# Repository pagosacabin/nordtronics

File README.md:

# Nordtronics

Code, hardware designs, and CAD models from **Nordtronics** (Pagosa Springs, CO) —
an off-grid solar, battery, and IoT practice. Custom LiFePO4 battery builds,
off-grid solar installs, and wireless sensor systems (ESP32 / LoRa / MQTT /
Home Assistant).

## Layout

- `backend/` — wildfire pipeline: Mosquitto broker, ingest worker, read-only
  FastAPI service, and the deployment guide (`DEPLOY.md`).
- `firmware/wildfire-node-v1/` — unified LoRa wildfire node/base-station
  firmware (Heltec LoRa 32 V4).
- `android/companion-v0/` — Android companion app for the wildfire network.
- `website/` — nordtronics.io site.
- `docs/` — runbooks and design docs (`docs/wildfire/` for the wildfire net).
- `firmware/cistern-monitor/` — Tank-Monitor remote cistern level monitor:
  ESP32-S3 + SX1262 LoRa TX/RX pair, ultrasonic level sensing, MQTT/Home
  Assistant integration (`cistern_unified.ino`).
- `firmware/lora-display/` — LoRa radio experiments on Heltec LoRa V3 boards,
  including display and RF-preset sketches.
- `python/ultrasonic-sensors/` — MicroPython scripts for ultrasonic distance
  sensing with OLED/LCD output.
- `hardware/battery-pcb/` — KiCad project archives for the custom main battery
  PCB (JK BMS based LiFePO4 pack), including versioned iterations.
- `hardware/busbar/` — Busbar designs for EVE 280Ah cells.
- `cad/first-project/` — Early KiCad project archives.
- `cad/robotic-arm/` — Robotic arm 3D model (STEP).

Archived `.zip` files are kept as-is, preserving the original design history.
- `installs/solar/` — Off-grid solar + storage install notes.

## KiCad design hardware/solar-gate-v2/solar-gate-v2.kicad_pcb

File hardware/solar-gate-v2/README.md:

# Solar gate — temperature cutoff, Mark 1 Rev 2

An add-in module for the wildfire-node power path: `panel (+) → this board → Heltec V4
solar input`. It switches the panel feed off when the cell is too cold or too hot, using a
10 k B3950 NTC bonded to the cell, an LM393 window comparator and a TL431 reference. The
pass element is two back-to-back FQP27P06 pairs (common drain at `M`), so the board blocks
current in both directions when off — that is what makes `P` never beep to `SOLAR_OUT`.

- **Board designation:** Mark 1 Rev 2 (silkscreen, title block)
- **Outline:** 85 × 60 mm, 2 layers, 1.6 mm, through-hole, 1 oz copper (Option B from
  `FORM-FACTOR-OPTIONS.md`, picked by Stephen 2026-11-16)
- **Off-board connections:** solder pads only — `P`, `GND`, `SOLAR_OUT`, `TH1` (NTC leads).
  JST GH is deferred to a future revision by Stephen's call.
- **Design current:** 3 A worst case through the Q1/Q2 pass paths (normal run ≈ 540 mA)

## Schematic source

The circuit is Stephen's as-built bench build. The card records it on 2026-11-16 as
**confirmed equal to the drawing**, with one qualification: the card's own LM393 pin 1 ↔
pin 5 note cannot be reconciled with the drawing from anything in the repo, and that
discrepancy is carried, unresolved, in "Open item for Stephen" below. Equivalence is
therefore asserted by the card for the circuit as a whole and *not* independently
established by this capture for that one node. Everything else here reproduces the
drawing net for net.

This capture starts from the last capture in the repo
(`origin/hermes/0075-solar-gate-v2-io-labels` @ `397f17d`,
`hardware/solar-gate-v2/solar-gate-v2.kicad_sch`) and re-draws it with the as-built parts:
four **FQP27P06** (TO-220) instead of AO3401, **BAT85** (DO-35) instead of BAT54, **LM393**
DIP-8, **TL431LP** TO-92, THT resistors/caps, and pad footprints on the four off-board nets.

Two numbering corrections came out of that re-draw and are deliberate:

1. **FQP27P06 pin numbers differ from AO3401.** AO3401 is G/S/D = 1/2/3; the TO-220
   FQP27P06 is **G/D/S = 1/2/3**. The net assignment follows the beep-out checklist, not the
   old symbol: all pin 2s (drains) at `M`, all pin 1s (gates) at `G`, Q1/Q2 pin 3s (sources)
   at `P`, Q3/Q4 pin 3s at `SOLAR_OUT`.
2. **TL431 pin numbers follow the TO-92 datasheet** (1 = REF, 2 = ANODE, 3 = CATHODE). The
   0075 capture used a project-local symbol numbered 1 = K, 2 = REF, 3 = A; the net result is
   identical (REF and K both on `VREF`, A on `GND`), but the standard KiCad symbol is correct
   for the physical part.

The connectivity was checked against the 0075 capture's netlist, net by net, after mapping the
pin numbers above: **14 nets, identical member sets** (see `docs/net-map.md`).

## Files

| Path | What |
|---|---|
| `solar-gate-v2.kicad_pro` | KiCad project (net classes: `Power_3A` 1.5 mm / 0.3 mm, `Gate` 0.5 mm) |
| `solar-gate-v2.kicad_sch` | Schematic, A3, Mark 1 Rev 2 title block |
| `solar-gate-v2.kicad_pcb` | PCB, 85 × 60 mm, routed 2-layer |
| `sym-lib-table`, `fp-lib-table` | Project library tables (comment-free; `KICAD10_*_DIR`) |
| `drc-report.rpt` | DRC run on the delivered board, `--severity-all --schematic-parity` |
| `fab/gerbers/` | Gerbers (F/B copper, mask, silkscreen, Edge.Cuts) + `.gbrjob` |
| `fab/drill/` | Excellon drill, separate PTH / NPTH |
| `fab/bom.csv` | BOM grouped by value + footprint (C3 = 47 µF 16 V, `CP_Radial_D5.0mm_P2.00mm`) |
| `renders/board-top.png`, `renders/board-bottom.png` | 3D renders, 2200 × 1500, for a phone |
| `renders/schematic.png` | Schematic sheet, 4961 × 3508 (A3 @ 300 dpi) |
| `docs/net-map.md` | Net list and the bench-name → designator map |

## Verification (as delivered)

- **ERC: 0 errors, 0 warnings** (`kicad-cli sch erc --severity-all --format report`).
- **DRC: 0 errors, 0 unconnected pads**, 2 warnings — both
  `lib_footprint_mismatch` on the rotated solder-pad footprints (J2, TH1); see below.
- **Schematic parity: 4 notes** — the four mounting holes are board-only (no schematic
  symbol), which is expected for a mechanical part.
- **Copper for 3 A:** IPC-2221 at 10 °C rise wants 1.37 mm of 1 oz external copper; the
  `Power_3A` net class routes `P`/`M`/`SOLAR_OUT` at **1.5 mm** and the `M` node is a
  **4 mm** bar between the two FET pairs (hand-drawn, not autorouted), with 2 mm stubs from
  each drain. The gate node `G`/`H` routes at 0.5 mm.
- Routing: 161 segments, 7 vias (6 of them GND stitching vias), 2 GND copper pours
  (F.Cu + B.Cu), both layers; all 14 nets connected (0 unconnected pads).

### Layout change 2026-11-17 (task 0205)

C1 (U1's supply bypass) moved from (30, 40) to (43.8, 48.6), against U1 pin 8: 5.83 mm
pad-centre to pad-centre where it was 21.9 mm, and the `P` copper between C1.1 and U1.8 is
now 5.8 mm of 1.5 mm trace instead of a 32 mm run through J1/D1. GND return is the pour
itself (C1.2 sits in it, with a stitching via 1.5 mm away). GND pours were added on both
layers (0.3 mm clearance, 0.5 mm thermal spokes) because the whole GND return — up to 3 A
between J1.2 and J2.2 — was previously a 0.2 mm trace run. Off-board labels were moved onto
their own pads, and U2's VREF strap was pushed to 1.05 mm clearance from pin 2 (was 0.20 mm).

### Rev 2 changes (task 0206, 2026-11-17)

Four review items, all Stephen's 2026-11-17 decisions:

1. **J1.2 and J2.2 are solid-connected to the GND pours** (pad-level `zone_connect 2`), so the
   full return no longer passes through four thermal spokes. Every other GND pad keeps thermal
   relief; the pours themselves are untouched (0.3 mm clearance, 0.3 mm gap, 0.5 mm spokes).
   Read back from the committed board: a 24-point sample ring at pad radius reports **24/24**
   points inside the fill on both layers for J1.2 and J2.2, and 6–12/24 (spokes only) for every
   other GND pad.
2. **C3, 47 µF 16 V input electrolytic, added at J1** — the only circuit change. `/P` gains
   C3.1 and `/GND` gains C3.2; nothing else moves (netlist diff below). It sits in the pocket
   between D1 (bottom edge y = 45.3) and U1 (top edge y = 51.4), centred at **(35.5, 48.3)**
   with pad 1 at (34.5, 48.3) and pad 2 at (36.5, 48.3) — i.e. the first clear pocket below the
   area C1 vacated at (30, 40), which is 0.3 mm from U1's pads and 1.8 mm from D1's pad and
   cannot take a 5 mm can. The `+` pad ties to the `P` trunk with one new 1.5 mm B.Cu segment
   (34.5, 48.3) → (30, 48.3); the `−` pad lands in the GND pour with a normal thermal relief.
   Courtyard gaps: 0.21 mm to D1, 0.35 mm to U1 — no overlap.
3. **Revision marks are REV 2**: silkscreen text `MARK 1 REV 2`, board and schematic title
   blocks (title and revision field).
4. **U2's reference designator** moved from (83.27, 51.0) to **(84.6, 47.0)** — 0.1 mm below the
   footprint courtyard, still under U2's right half, 2.5 mm clear of Q5's courtyard and 1.5 mm
   clear of the `MARK 1 REV 2` text.

**Footprint substitution, declared.** The card named `Capacitor_THT:C_Radial_D5.0mm_P2.00mm`;
KiCad 10 has no such footprint. The only 5 mm / 2 mm-pitch radial parts are
`C_Radial_D5.0mm_H{5,7,11}.0mm_P2.00mm` (unpolarized ceramic/film) and
`CP_Radial_D5.0mm_P2.00mm` (polarized electrolytic). A 47 µF electrolytic is polarized, so the
can assumed is **`CP_Radial_D5.0mm_P2.00mm` — 5 mm diameter, 7 mm height, 2 mm pitch**, with the
matching polarized symbol `Device:C_Polarized` (pin 1 = `+`). If Stephen's stocked part is a
taller can (5 × 11 mm), swap the footprint; the pads and the placement do not move. The
footprint's own silkscreen carries the `+` mark beside pad 1 (the 0.5 mm cross at
(32.95, 46.83)); no duplicate mark was added.

Verification for this revision: ERC **0 errors / 0 warnings**; DRC **2 warnings, 0 errors,
0 unconnected pads, 4 extra-footprint notes** — the same two `lib_footprint_mismatch` warnings
on J2/TH1 as Rev 1 and nothing new. Netlist versus Rev 1 (`f4f6edb`): 14 nets both sides,
`/P` +C3.1, `/GND` +C3.2, no other membership change. Render diff against the Rev 1 renders
confines every changed pixel cluster to the four intended areas (C3, the `REV 2` digit, U2's
label at its old and new positions, and the J1.2/J2.2 pad copper).

### The 2 remaining DRC warnings, justified

`[lib_footprint_mismatch]` on J2 and TH1 only (the same footprint at rotation 0 — J1 — is
clean). Probed, not assumed: a scratch copy with J2/TH1 forced to rotation 0 reports **no**
`lib_footprint_mismatch`, so the warning is triggered by the rotation of a pad-only
(no-copper-annulus) footprint during KiCad's library comparison. The board file itself is
authoritative for fabrication; the Gerbers are plotted from it, and the pad geometry
(4.0 mm pad, 3.0 mm drill, 7.2 mm pitch) is byte-identical to the library.

## LM393 pin 1 ↔ pin 5 — resolved (2026-11-17)

Stephen resolved the open item: the pin 1 ↔ pin 5 tie was a jumper he had added on his own
bench build from a misread while wiring the breadboard, and he removed it. It was never a
schematic feature — the drawing (pin 1 on `OA`, pin 5 on `N`) is right and this capture is
correct as delivered. No board or schematic change follows from it.

## Fabrication notes

2-layer, 1.6 mm FR-4, 1 oz copper, HASL, green mask. Minimum trace 0.2 mm, minimum clearance
0.2 mm, 0.3 mm on the 3 A nets. Plated through holes for all parts; the 3.0 mm wire-pad holes
take 1.5–2.5 mm² wire. Four M3 mounting holes (3.2 mm, no annular ring) 5 mm in from the
corners. Silkscreen marks every off-board pad (`P +`, `GND`, `SOLAR_OUT +5V`, `NTC CELL`) and
the board designation.

## Rebuilding

```bash
cd hardware/solar-gate-v2
kicad-cli sch erc --severity-all --format report --output erc.rpt solar-gate-v2.kicad_sch
kicad-cli pcb drc --severity-all --schematic-parity --output drc-report.rpt solar-gate-v2.kicad_pcb
kicad-cli pcb export gerbers --output fab/gerbers/ \
  -l F.Cu,B.Cu,F.SilkS,B.SilkS,F.Mask,B.Mask,Edge.Cuts solar-gate-v2.kicad_pcb
kicad-cli pcb export drill --output fab/drill/ --format excellon --excellon-units mm \
  --excellon-separate-th solar-gate-v2.kicad_pcb
kicad-cli pcb render --output renders/board-top.png --side top --width 2200 --height 1500 \
  --quality high --background opaque solar-gate-v2.kicad_pcb
```

Built with KiCad 10.0.8 and the KiCad MCP server; geometry and connectivity were verified
programmatically (netlist diff, DRC, courtyard/pad collision checks), not by eye.

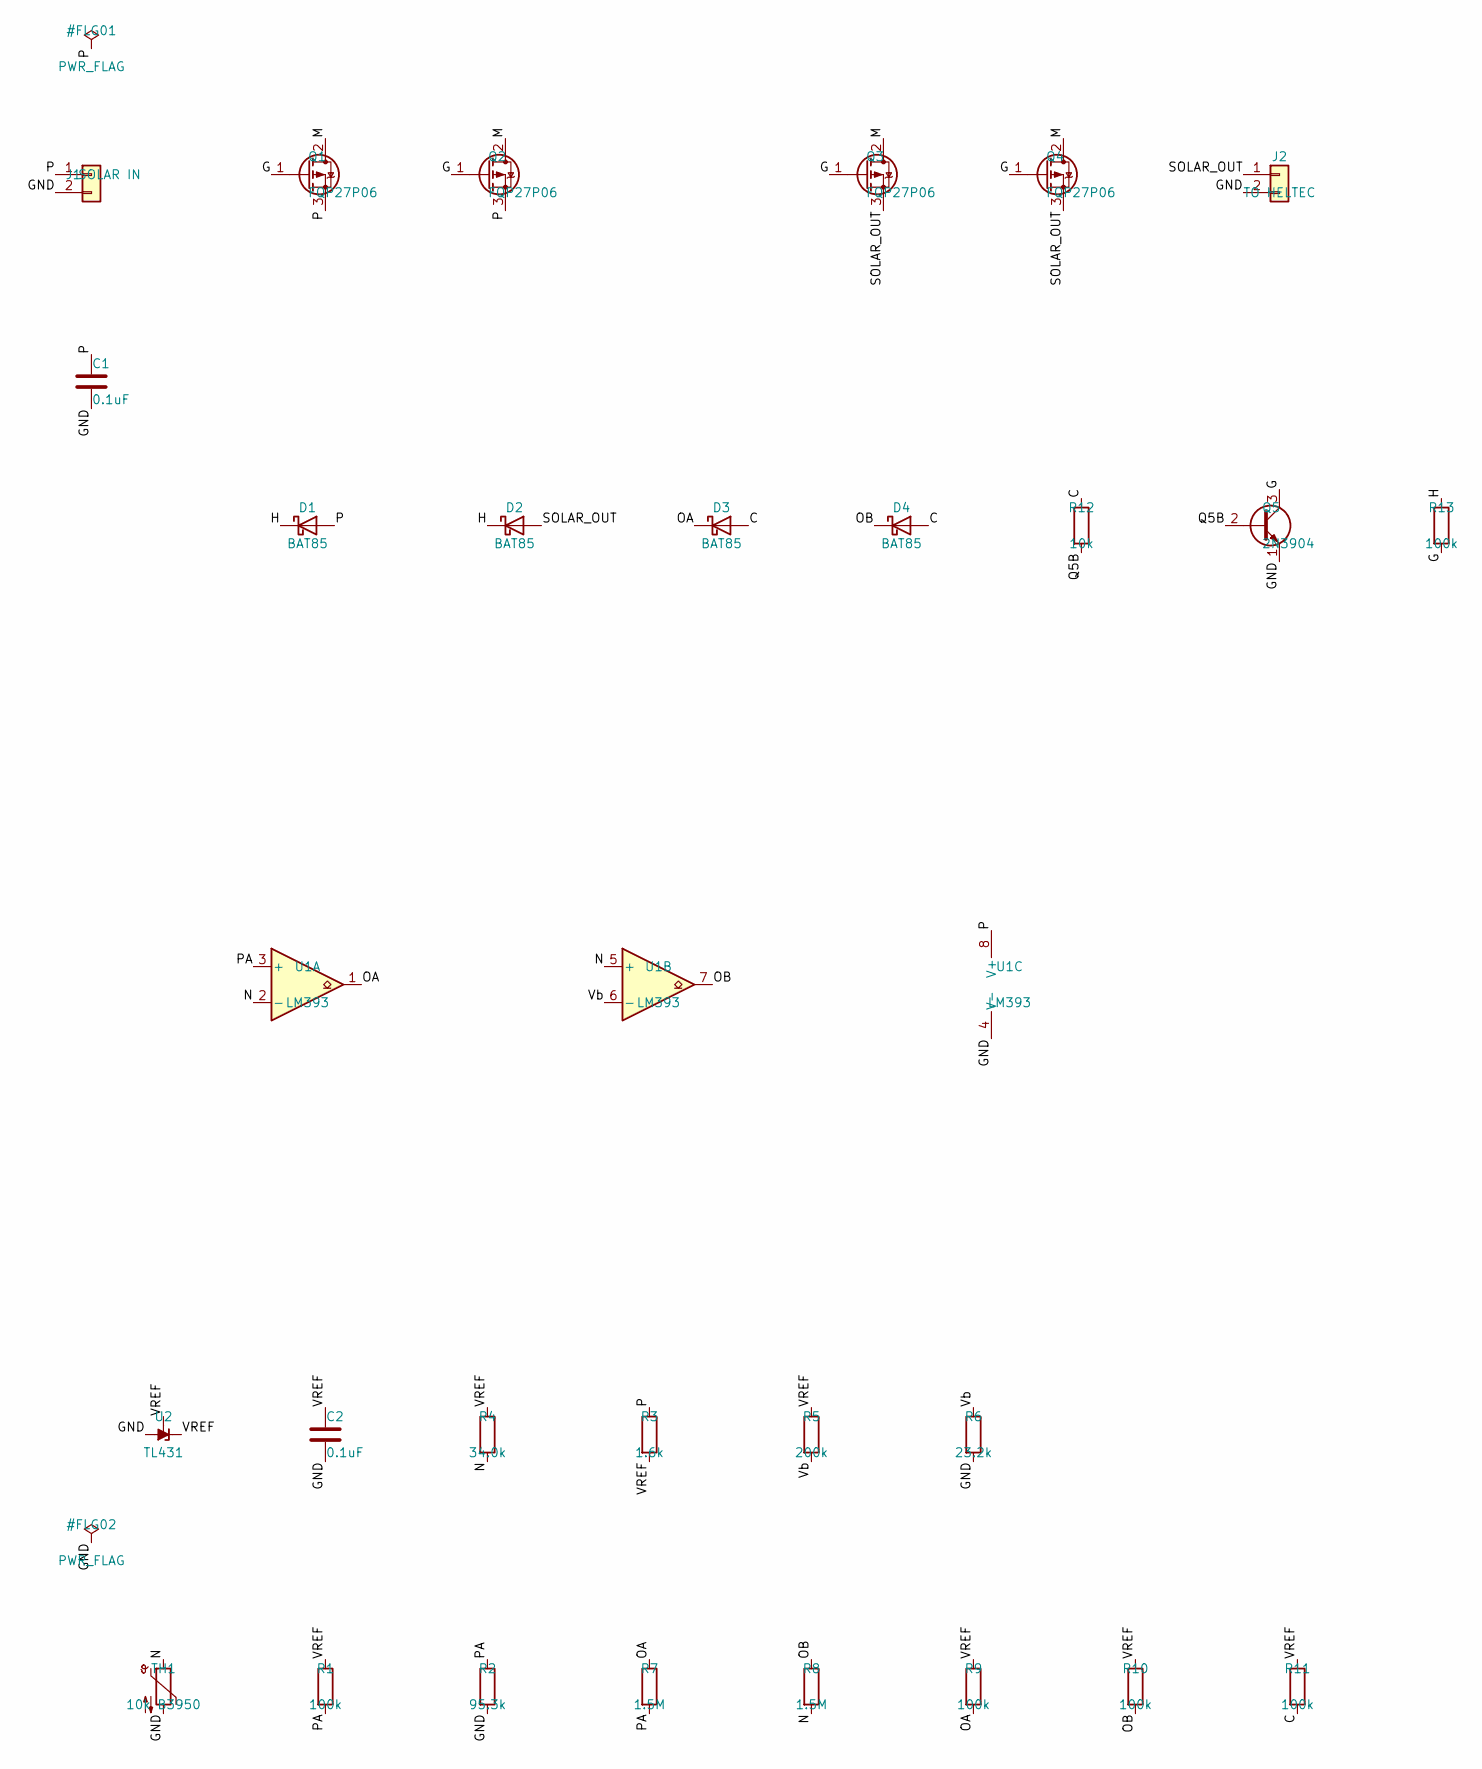
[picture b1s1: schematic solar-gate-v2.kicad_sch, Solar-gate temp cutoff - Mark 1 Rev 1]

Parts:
C1, C2: 0.1uF; C_Disc_D5.0mm_W2.5mm_P5.00mm
D1, D2, D3, D4: BAT85; D_DO-35_SOD27_P7.62mm_Horizontal
J1: SOLAR IN; SolderWire-2.5sqmm_1x02_P7.2mm_D2.4mm_OD3.6mm
J2: TO HELTEC; SolderWire-2.5sqmm_1x02_P7.2mm_D2.4mm_OD3.6mm
Q1, Q2, Q3, Q4: FQP27P06; TO-220-3_Vertical
Q5: 2N3904; TO-92_Inline
R1, R9, R10, R11, R13: 100k; R_Axial_DIN0207_L6.3mm_D2.5mm_P10.16mm_Horizontal
R2: 95.3k; R_Axial_DIN0207_L6.3mm_D2.5mm_P10.16mm_Horizontal
R3: 1.6k; R_Axial_DIN0207_L6.3mm_D2.5mm_P10.16mm_Horizontal
R4: 34.0k; R_Axial_DIN0207_L6.3mm_D2.5mm_P10.16mm_Horizontal
R5: 200k; R_Axial_DIN0207_L6.3mm_D2.5mm_P10.16mm_Horizontal
R6: 23.2k; R_Axial_DIN0207_L6.3mm_D2.5mm_P10.16mm_Horizontal
R7, R8: 1.5M; R_Axial_DIN0207_L6.3mm_D2.5mm_P10.16mm_Horizontal
R12: 10k; R_Axial_DIN0207_L6.3mm_D2.5mm_P10.16mm_Horizontal
TH1: 10k B3950; SolderWire-2.5sqmm_1x02_P7.2mm_D2.4mm_OD3.6mm
U1: LM393; DIP-8_W7.62mm
U2: TL431; TO-92_Inline

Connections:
/C: D3.2 (A), D4.2 (A), R11.2, R12.1
/G: Q1.1 (G), Q2.1 (G), Q3.1 (G), Q4.1 (G), Q5.3 (C), R13.2
/GND: C1.2, C2.2, J1.2, J2.2, Q5.1 (E), R2.2, R6.2, TH1.2, U1.4 (V-), U2.2 (A); also elsewhere on the board
/H: D1.1 (K), D2.1 (K), R13.1
/M: Q1.2 (D), Q2.2 (D), Q3.2 (D), Q4.2 (D)
/N: R4.2, R8.2, TH1.1, U1.2 (-), U1.5 (+)
/OA: D3.1 (K), R7.1, R9.2, U1.1
/OB: D4.1 (K), R8.1, R10.2, U1.7
/P: C1.1, D1.2 (A), J1.1, Q1.3 (S), Q2.3 (S), R3.1, U1.8 (V+); also elsewhere on the board
/PA: R1.2, R2.1, R7.2, U1.3 (+)
/Q5B: Q5.2 (B), R12.2
/SOLAR_OUT: D2.2 (A), J2.1, Q3.3 (S), Q4.3 (S)
/VREF: C2.1, R1.1, R3.2, R4.1, R5.1, R9.1, R10.1, R11.1, U2.1 (REF), U2.3 (K)
/Vb: R5.2, R6.1, U1.6 (-)

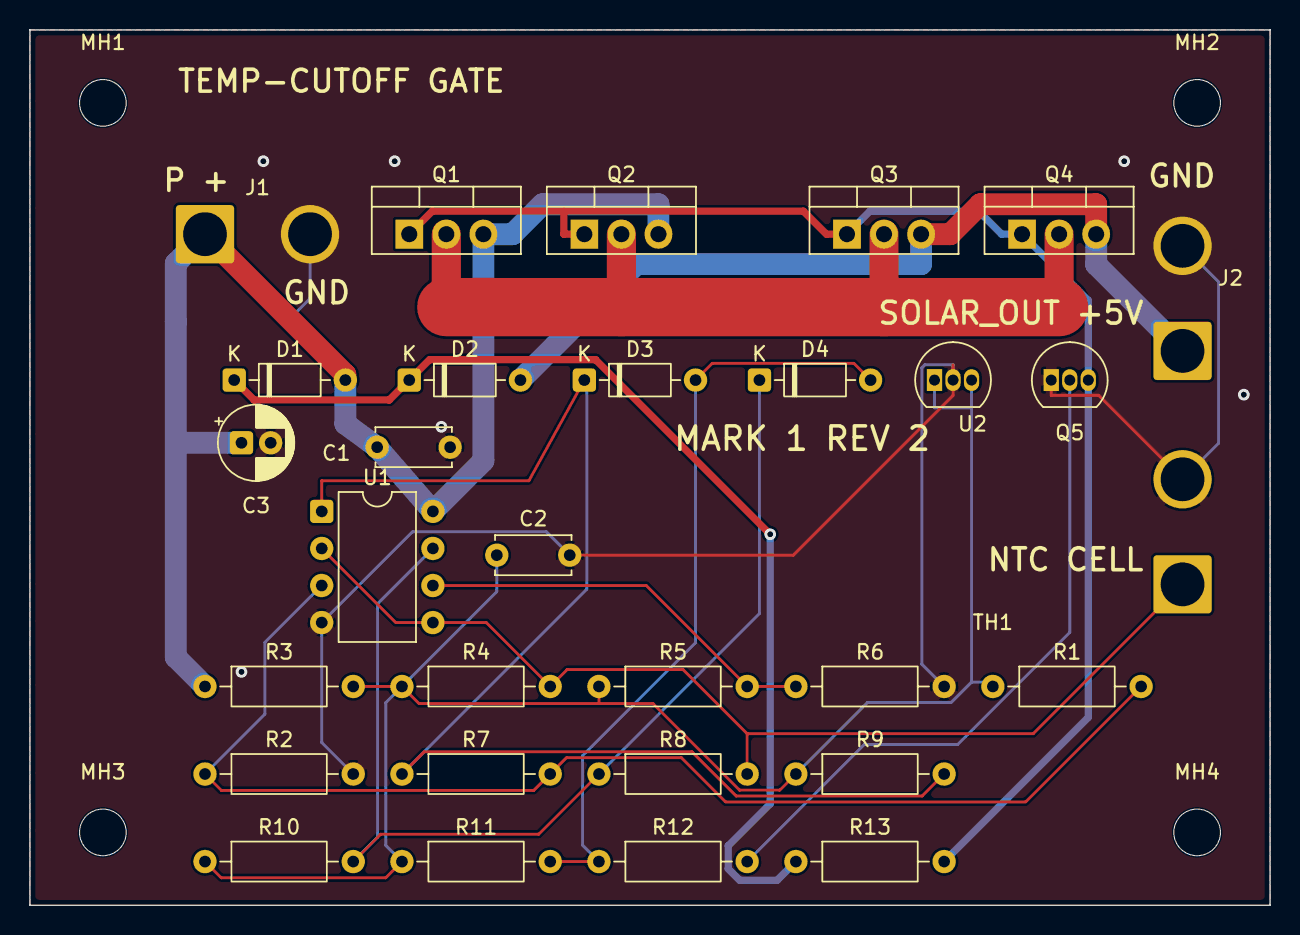
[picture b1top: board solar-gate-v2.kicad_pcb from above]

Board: 2 copper layers, 85.0 x 60.0 mm, 34 parts (0 on the bottom side), 14 nets.

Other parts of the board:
C3: 47uF 16V; CP_Radial_D5.0mm_P2.00mm
MH1, MH2, MH3, MH4: MountingHole_3.2mm_M3

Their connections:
/GND: C3.2; also elsewhere on the board
/P: C3.1; also elsewhere on the board

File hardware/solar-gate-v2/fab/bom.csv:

"Reference","Value","Footprint"
"C1,C2","0.1uF","Capacitor_THT:C_Disc_D5.0mm_W2.5mm_P5.00mm"
"D1-D4","BAT85","Diode_THT:D_DO-35_SOD27_P7.62mm_Horizontal"
"J1","SOLAR IN","Connector_Wire:SolderWire-2.5sqmm_1x02_P7.2mm_D2.4mm_OD3.6mm"
"J2","TO HELTEC","Connector_Wire:SolderWire-2.5sqmm_1x02_P7.2mm_D2.4mm_OD3.6mm"
"Q1-Q4","FQP27P06","Package_TO_SOT_THT:TO-220-3_Vertical"
"Q5","2N3904","Package_TO_SOT_THT:TO-92_Inline"
"R1,R9-R11,R13","100k","Resistor_THT:R_Axial_DIN0207_L6.3mm_D2.5mm_P10.16mm_Horizontal"
"R2","95.3k","Resistor_THT:R_Axial_DIN0207_L6.3mm_D2.5mm_P10.16mm_Horizontal"
"R3","1.6k","Resistor_THT:R_Axial_DIN0207_L6.3mm_D2.5mm_P10.16mm_Horizontal"
"R4","34.0k","Resistor_THT:R_Axial_DIN0207_L6.3mm_D2.5mm_P10.16mm_Horizontal"
"R5","200k","Resistor_THT:R_Axial_DIN0207_L6.3mm_D2.5mm_P10.16mm_Horizontal"
"R6","23.2k","Resistor_THT:R_Axial_DIN0207_L6.3mm_D2.5mm_P10.16mm_Horizontal"
"R7,R8","1.5M","Resistor_THT:R_Axial_DIN0207_L6.3mm_D2.5mm_P10.16mm_Horizontal"
"R12","10k","Resistor_THT:R_Axial_DIN0207_L6.3mm_D2.5mm_P10.16mm_Horizontal"
"TH1","10k B3950","Connector_Wire:SolderWire-2.5sqmm_1x02_P7.2mm_D2.4mm_OD3.6mm"
"U1","LM393","Package_DIP:DIP-8_W7.62mm"
"U2","TL431","Package_TO_SOT_THT:TO-92_Inline"

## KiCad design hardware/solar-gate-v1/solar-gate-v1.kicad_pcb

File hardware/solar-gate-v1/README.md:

# solar-gate-v1 — solar cold-charge gate (EDA flow test vehicle)

**TEST BOARD ONLY. Not production, not reviewed, no Gerbers, no fab output.**

This project exists to cold-test the schematic → layout → autoroute rung of the
toolchain against a real circuit. The circuit itself is the approved solar
cold-charge gate spec, but nothing here has been bench-validated and nothing
should be built from it until Stephen has reviewed both the schematic and the
layout.

## Circuit

Warm → NTC low → `VA < VTH` → comparator output pulls `GATE` low → Q1 on.
Cold / no sun → `GATE` floats to `Panel+` through Rg → Q1 off.

| Ref | Part | Package | Notes |
|-----|------|---------|-------|
| Q1  | AO3401 (P-ch MOSFET) | SOT-23 | 1=G, 2=S, 3=D |
| U1  | TLV3401 (nanopower comparator, open-drain) | **SOT-23-5** | see pinout note below |
| D1  | TL431 (2.5 V shunt reference) | SOT-23-3 | 1=K, 2=REF, 3=A (TI DBZ); REF tied to K |
| TH1 | 10k NTC B=3950, **off-board** → 2-pin JST GH 1.25 mm | — | board-edge connector |
| Rs  | 12k | 0805 | Panel+ → REF2V5 |
| R1, R2, R3 | 30k | 0805 | VA / VTH dividers |
| Rf  | 270k | 0805 | GATE → VA feedback |
| Rg  | 100k | 0805 | Panel+ → GATE pull-up |
| R4, R5 | 100k | 0805 | telemetry divider, GATE → GPIO |
| C1  | 100nF | 0805 | across D1 |
| C2  | 10nF | 0805 | VA → GND |
| J1, J2, J4 | JST GH 1.25 mm 2-pin | — | panel in / charger out / telemetry out |

Nets: `Panel+`, `GND`, `REF2V5`, `VA`, `VTH`, `GATE`, `CHG+`, `TELEM`.

### D1 reference — TL431 (task 0043)

The first pass drew D1 as a TLV431, whose `VREF` is 1.24 V, so the
`REF2V5`/`VTH` targets did not hold (0039 open item 1). D1 is now a **TL431**
(TI SLVS543S, DBZ SOT-23-3: **1 = K, 2 = REF, 3 = A**), with the divider values
left as computed for 2.5 V.

The board did not change. `REF` and `K` are both on `REF2V5` by design, so
D1 pad 1 (K) and pad 2 (REF) were already shorted on that net, pad 3 (A) was
already on `GND`, and the footprint is the same `Package_TO_SOT_SMD:SOT-23`.
`solar-gate-v1.kicad_pcb` is byte-identical to the 0039 tip
(`sha256 95c7c0b279688f20cd8d84435e144e05e4ca9093e4f3c9af582df41f32b13893`).
Note the pinout trap: a TLV431 in DBZ is 1=REF / 2=CATHODE / 3=ANODE, the
*opposite* of the TL431 in the same package — the two are interchangeable here
only because REF and K are tied together.

Bias current: the TL431 needs 0.4–1 mA of cathode current to regulate
(TLV431: 55–80 µA), and `Rs` = 12k from `Panel+` sets that current. The
implication is reported in the 0043 reply; no bias-network or divider change
was made.

## Board

2-layer, 40 × 30 mm, 1 oz copper, all parts on the front. Power path along the
top edge (J1 → Q1 → J2); TH1 and J4 on board edges; NTC is off-board.

Track widths (IPC-2221, external layer, 1 oz, 10 °C rise):

| Net class | Nets | Width | Rationale |
|-----------|------|-------|-----------|
| `POWER_1A` | `Panel+`, `CHG+`, `GND` | **0.80 mm** | 1 A needs 0.30 mm minimum; 0.8 mm ≈ 2.0 A capability |
| `SIGNAL_0R25` | `VA`, `VTH`, `GATE`, `REF2V5`, `TELEM` | 0.25 mm (routed at 0.20 mm, see below) | signal only |

`GND` is in the high-current class because it carries the 1 A return
(panel− → charger−).

## How it was built

Entirely through the KiCad MCP server (mixelpixx/KiCAD-MCP-Server 2.7.0) —
project/schematic creation, symbol authoring, wiring, ERC, board sync,
placement, autoroute via Freerouting 2.4.1, and DRC. No hand-edited KiCad
files, no hand-routing.

- ERC: `solar-gate-v1-erc.txt` — **0 errors, 0 warnings**
- DRC: `solar-gate-v1_drc_violations.json` — **2 errors, 0 warnings**
  (both are Freerouting fanout stubs at 0.15 mm on net `VA`, below the
  declared 0.20 mm minimum — router output, left as-is and reported)
- Autoroute: `solar-gate-v1.dsn` / `solar-gate-v1.ses`. Freerouting reported
  `0 unrouted and 0 violations`, final score 999.99; fanout escaped 39/39 SMD
  pins. 117 segments, 11 vias on the board; all 8 nets have copper.

## Open items for review

1. **Resolved in 0043 — D1 is now a TL431, a true 2.5 V reference.** With REF
   tied to K the reference node sits at 2.5 V, so R2/R3 halve it to the
   specified 1.25 V and the divider values stand. What replaces it as a live
   question is bias current: the TL431 needs 0.4–1 mA of cathode current to
   regulate where the TLV431 needed 55–80 µA, and `Rs` = 12k sets that current
   from `Panel+`. Numbers are in the 0043 reply; nothing was re-scaled.
2. **U1 pin 5 = VCC, pin 2 = GND, pin 3 = IN+, pin 4 = IN−** (TLV3401 has no
   SC-70-5 package; the spec's SC-70-5 call was corrected to SOT-23-5).
3. **J4 (telemetry out) is an addition** — the spec listed only panel in,
   GND and charger out, but `TELEM` has to leave the board somehow.
4. `SIGNAL_0R25` never took effect: those five nets fell back to the board's
   `Default` class and were routed at 0.20 mm (still fine for signals).
5. Two DRC `track_width` errors are unresolved router output, deliberately not
   hand-fixed.

## Environment notes

The Flatpak KiCad 10 sandbox has its own `/usr`, so host library paths are
invisible to it:

- `fp-lib-table` in this directory points at the Flatpak **KiCad 10 footprint
  runtime** (`/var/lib/flatpak/runtime/.../footprints/...`), a host path both
  the host `pcbnew` backend and the sandboxed `kicad-cli` 10 can read. Pointing
  at `/usr/share/kicad/footprints` instead makes ERC/DRC report every footprint
  library as "not enabled in the current configuration".
- `sym-lib-table` now points the project library at
  `${KIPRJMOD}/solar-gate-v1.kicad_sym` instead of an absolute checkout path.
  The old absolute path broke ERC the moment the project was opened from any
  other checkout or worktree: `kicad-cli` reported `The symbol library
  'solar-gate-v1' was not found at '<abs path>'` for every project symbol.
- The MCP server's symbol loader needs `KICAD_SYMBOL_DIR` set to the same
  runtime's `symbols/` directory, or the schematic's cached symbols are written
  from the host KiCad 9 libraries and every symbol then mismatches the KiCad 10
  library the ERC engine reads.

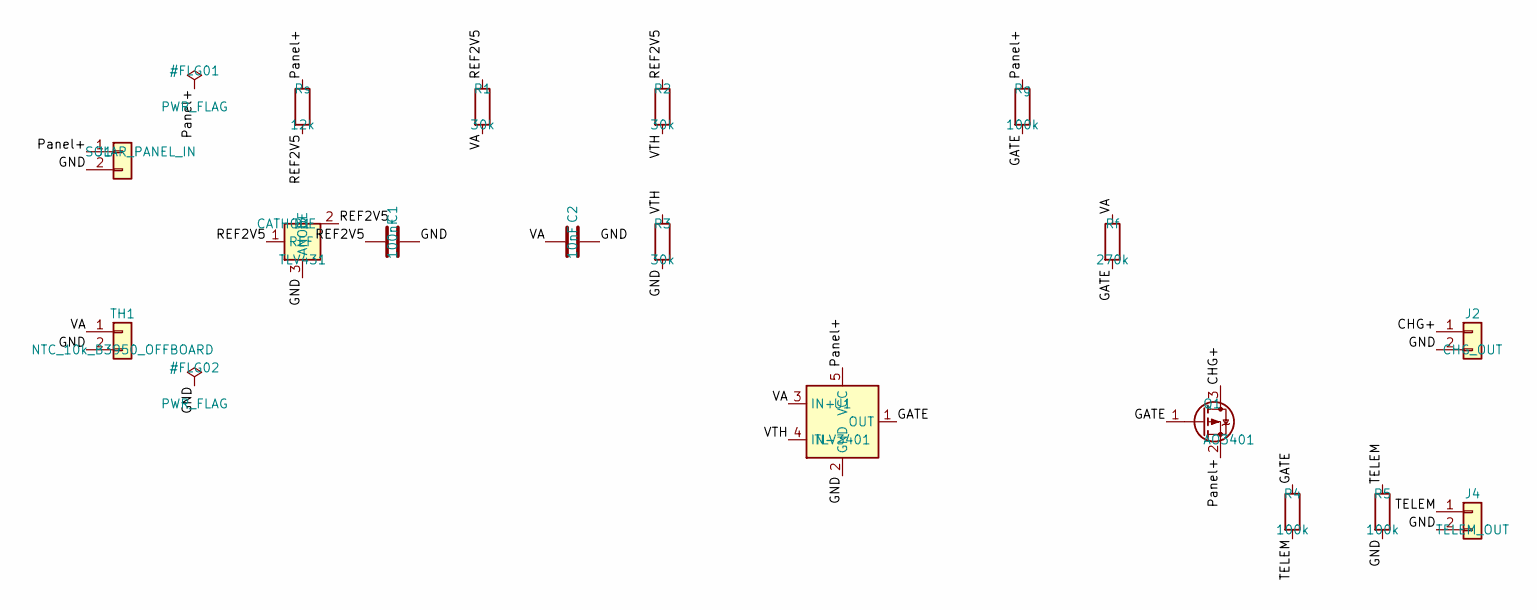
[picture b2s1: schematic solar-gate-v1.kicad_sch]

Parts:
C1: 100nF; C_0805_2012Metric
C2: 10nF; C_0805_2012Metric
D1: TLV431; SOT-23
J1: SOLAR_PANEL_IN; JST_GH_BM02B-GHS-TBT_1x02-1MP_P1.25mm_Vertical
J2: CHG_OUT; JST_GH_BM02B-GHS-TBT_1x02-1MP_P1.25mm_Vertical
J4: TELEM_OUT; JST_GH_BM02B-GHS-TBT_1x02-1MP_P1.25mm_Vertical
Q1: AO3401; SOT-23
R1, R2, R3: 30k; R_0805_2012Metric
R4, R5: 100k; R_0805_2012Metric
Rf: 270k; R_0805_2012Metric
Rg: 100k; R_0805_2012Metric
Rs: 12k; R_0805_2012Metric
TH1: NTC_10k_B3950_OFFBOARD; JST_GH_BM02B-GHS-TBT_1x02-1MP_P1.25mm_Vertical
U1: TLV3401; SOT-23-5

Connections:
CHG+: J2.1, Q1.3 (D)
GATE: Q1.1 (G), R4.1, Rf.2, Rg.2, U1.1 (OUT)
GND: C1.2, C2.2, D1.3 (ANODE), J1.2, J2.2, J4.2, R3.2, R5.2, TH1.2, U1.2 (GND)
Panel+: J1.1, Q1.2 (S), Rg.1, Rs.1, U1.5 (VCC)
REF2V5: C1.1, D1.1 (REF), D1.2 (CATHODE), R1.1, R2.1, Rs.2
TELEM: J4.1, R4.2, R5.1
VA: C2.1, R1.2, Rf.1, TH1.1, U1.3 (IN+)
VTH: R2.2, R3.1, U1.4 (IN-)

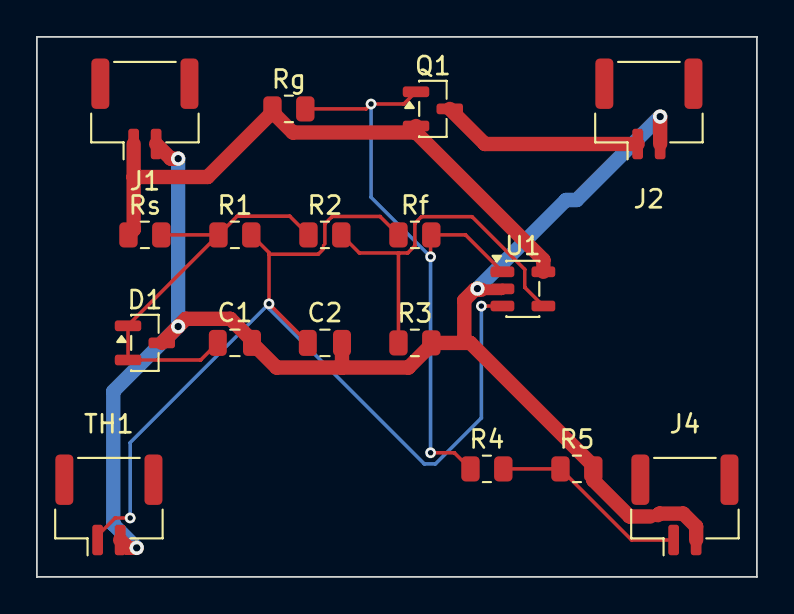
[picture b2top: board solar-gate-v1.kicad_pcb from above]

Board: 2 copper layers, 40.0 x 30.0 mm, 17 parts (0 on the bottom side), 8 nets.

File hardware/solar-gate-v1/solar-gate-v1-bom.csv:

value,footprint,quantity,references
SOLAR_PANEL_IN,Connector_JST:JST_GH_BM02B-GHS-TBT_1x02-1MP_P1.25mm_Vertical,1,['J1']
100k,Resistor_SMD:R_0805_2012Metric,3,"['Rg', 'R4', 'R5']"
CHG_OUT,Connector_JST:JST_GH_BM02B-GHS-TBT_1x02-1MP_P1.25mm_Vertical,1,['J2']
12k,Resistor_SMD:R_0805_2012Metric,1,['Rs']
NTC_10k_B3950_OFFBOARD,Connector_JST:JST_GH_BM02B-GHS-TBT_1x02-1MP_P1.25mm_Vertical,1,['TH1']
TLV431,Package_TO_SOT_SMD:SOT-23,1,['D1']
AO3401,Package_TO_SOT_SMD:SOT-23,1,['Q1']
TLV3401,Package_TO_SOT_SMD:SOT-23-5,1,['U1']
270k,Resistor_SMD:R_0805_2012Metric,1,['Rf']
30k,Resistor_SMD:R_0805_2012Metric,3,"['R3', 'R2', 'R1']"
100nF,Capacitor_SMD:C_0805_2012Metric,1,['C1']
TELEM_OUT,Connector_JST:JST_GH_BM02B-GHS-TBT_1x02-1MP_P1.25mm_Vertical,1,['J4']
10nF,Capacitor_SMD:C_0805_2012Metric,1,['C2']
